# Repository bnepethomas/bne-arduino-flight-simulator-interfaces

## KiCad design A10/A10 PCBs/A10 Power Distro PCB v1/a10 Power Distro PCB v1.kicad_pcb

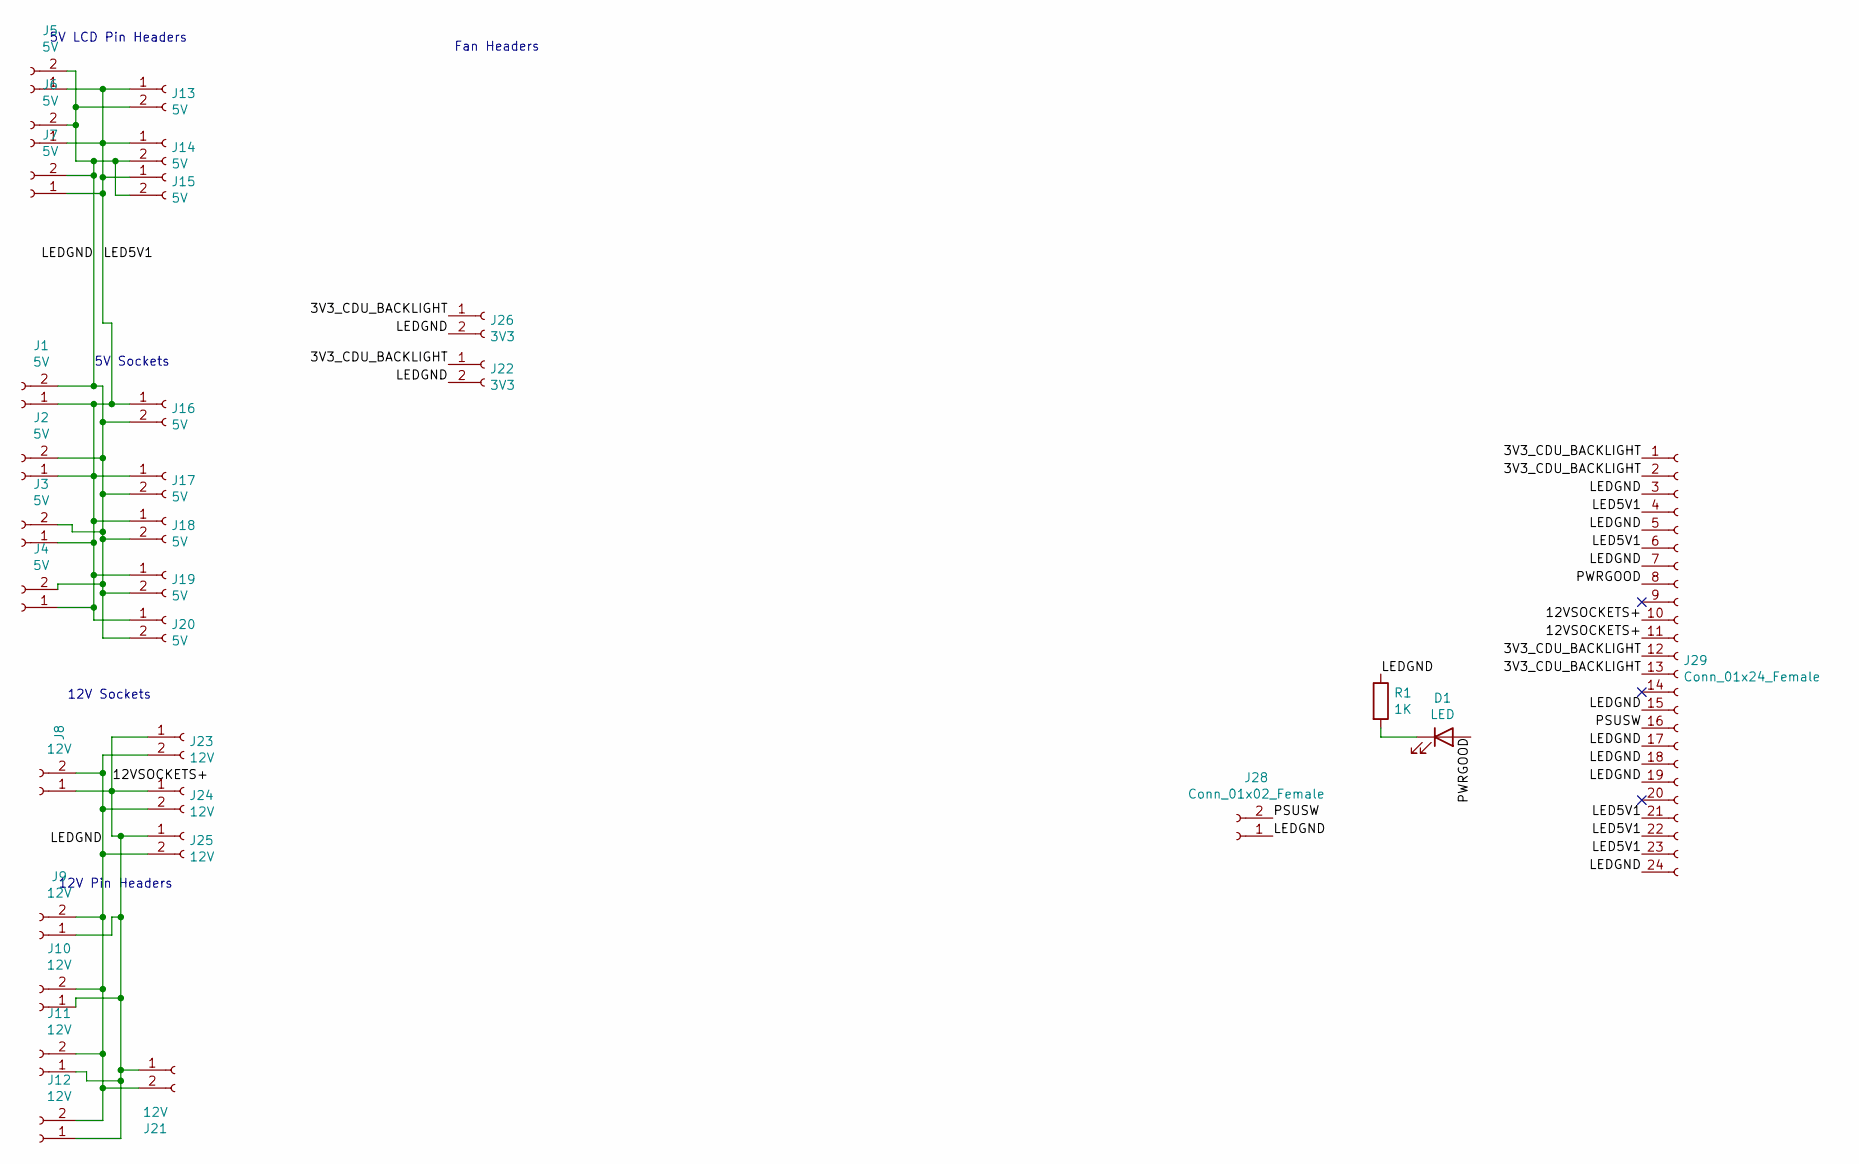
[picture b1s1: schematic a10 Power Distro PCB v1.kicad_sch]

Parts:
D1: LED; LED_D3.0mm
J1, J2, J3, J4, J16, J17, J18: 5V; BarrelJack_Horizontal
J5, J6, J7, J13, J14, J15, J19, J20: 5V; Molex_KK-254_AE-6410-02A_1x02_P2.54mm_Vertical
J8, J11, J12, J23, J24, J25: 12V; BarrelJack_Horizontal
J9, J10, J21: 12V; Molex_KK-254_AE-6410-02A_1x02_P2.54mm_Vertical
J22: 3V3; BarrelJack_Horizontal
J26: 3V3; Molex_KK-254_AE-6410-02A_1x02_P2.54mm_Vertical
J28: Conn_01x02_Female; Molex_KK-254_AE-6410-02A_1x02_P2.54mm_Vertical
J29: Conn_01x24_Female; Molex_Mini-Fit_Jr_5566-24A_2x12_P4.20mm_Vertical
R1: 1K; R_Axial_DIN0207_L6.3mm_D2.5mm_P7.62mm_Horizontal

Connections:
/3V3_CDU_BACKLIGHT: J22.1, J26.1, J29.1, J29.2, J29.12, J29.13
/12VSOCKETS+: J8.1, J9.1, J10.1, J11.1, J12.1, J21.1, J23.1, J24.1, J25.1, J29.10, J29.11
/LED5V1: J1.1, J2.1, J3.1, J4.1, J5.1, J6.1, J7.1, J13.1, J14.1, J15.1, J16.1, J17.1, J18.1, J19.1, J20.1, J29.4, J29.6, J29.21, J29.22, J29.23
/LEDGND: J1.2, J2.2, J3.2, J4.2, J5.2, J6.2, J7.2, J8.2, J9.2, J10.2, J11.2, J12.2, J13.2, J14.2, J15.2, J16.2, J17.2, J18.2, J19.2, J20.2, J21.2, J22.2, J23.2, J24.2, J25.2, J26.2, J28.1, J29.3, J29.5, J29.7, J29.15, J29.17, J29.18, J29.19, J29.24, R1.1
/PSUSW: J28.2, J29.16
/PWRGOOD: D1.2 (A), J29.8
unnamed: D1.1 (K), R1.2

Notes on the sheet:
Fan Headers
12V Pin Headers
5V LCD Pin Headers
12V Sockets
5V Sockets

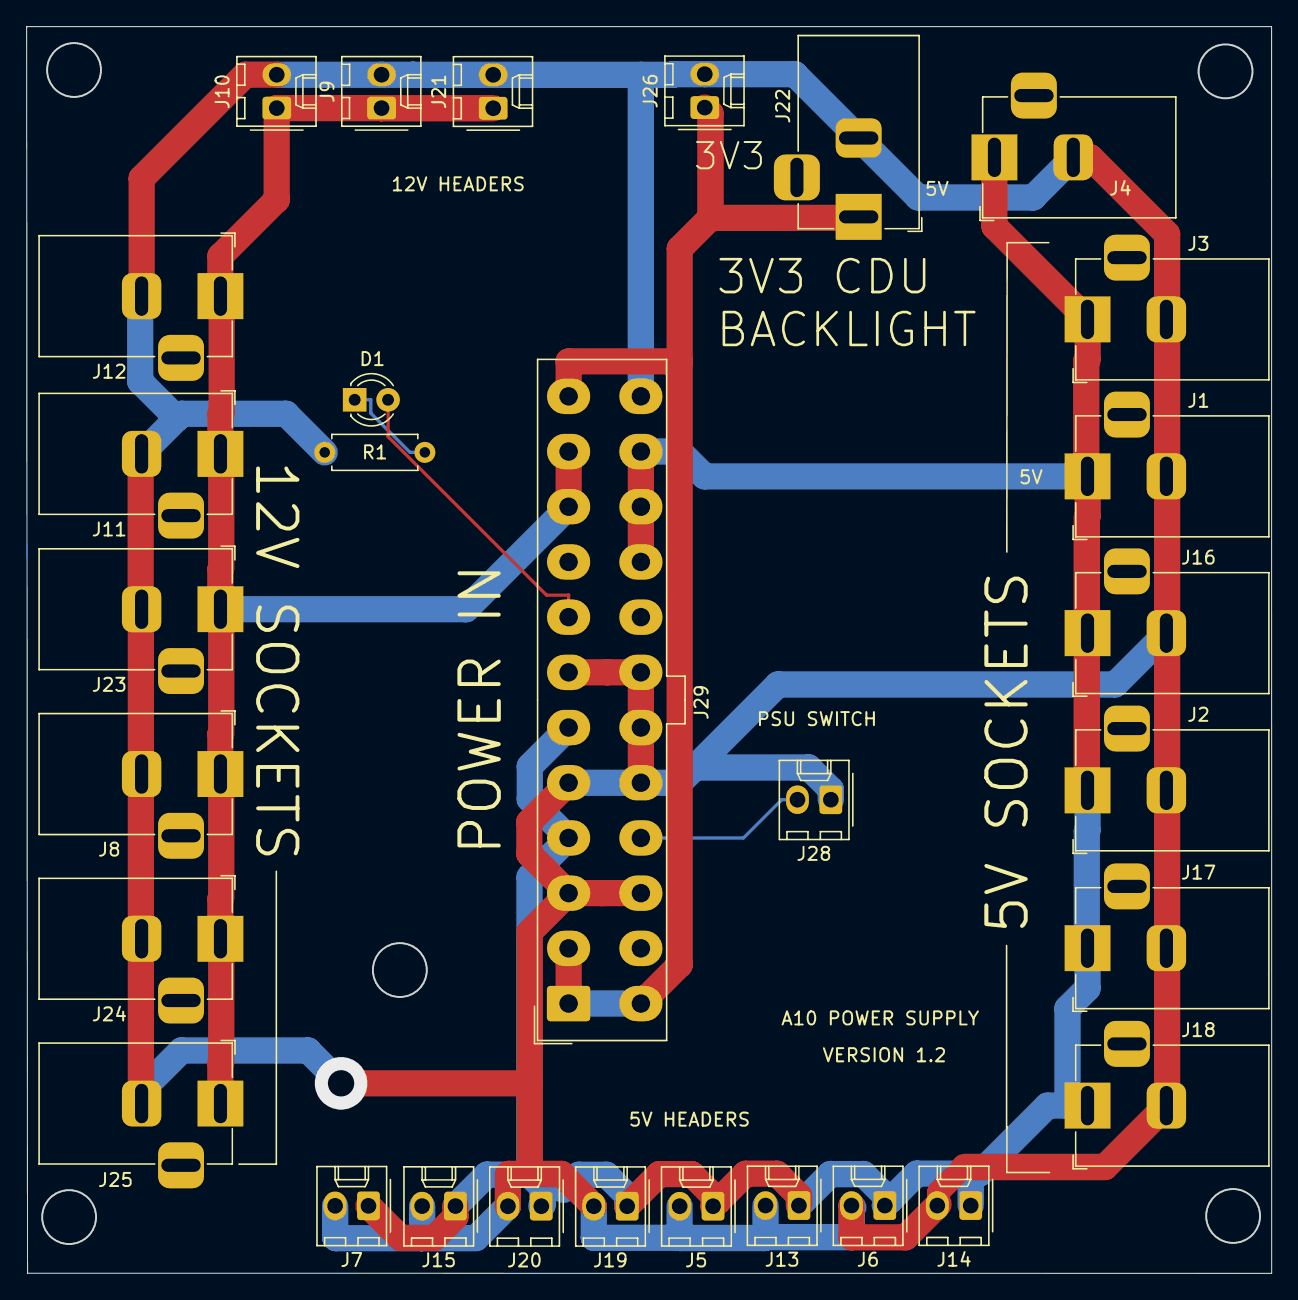
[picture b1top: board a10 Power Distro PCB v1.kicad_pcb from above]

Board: 2 copper layers, 94.7 x 94.9 mm, 30 parts (0 on the bottom side), 7 nets.

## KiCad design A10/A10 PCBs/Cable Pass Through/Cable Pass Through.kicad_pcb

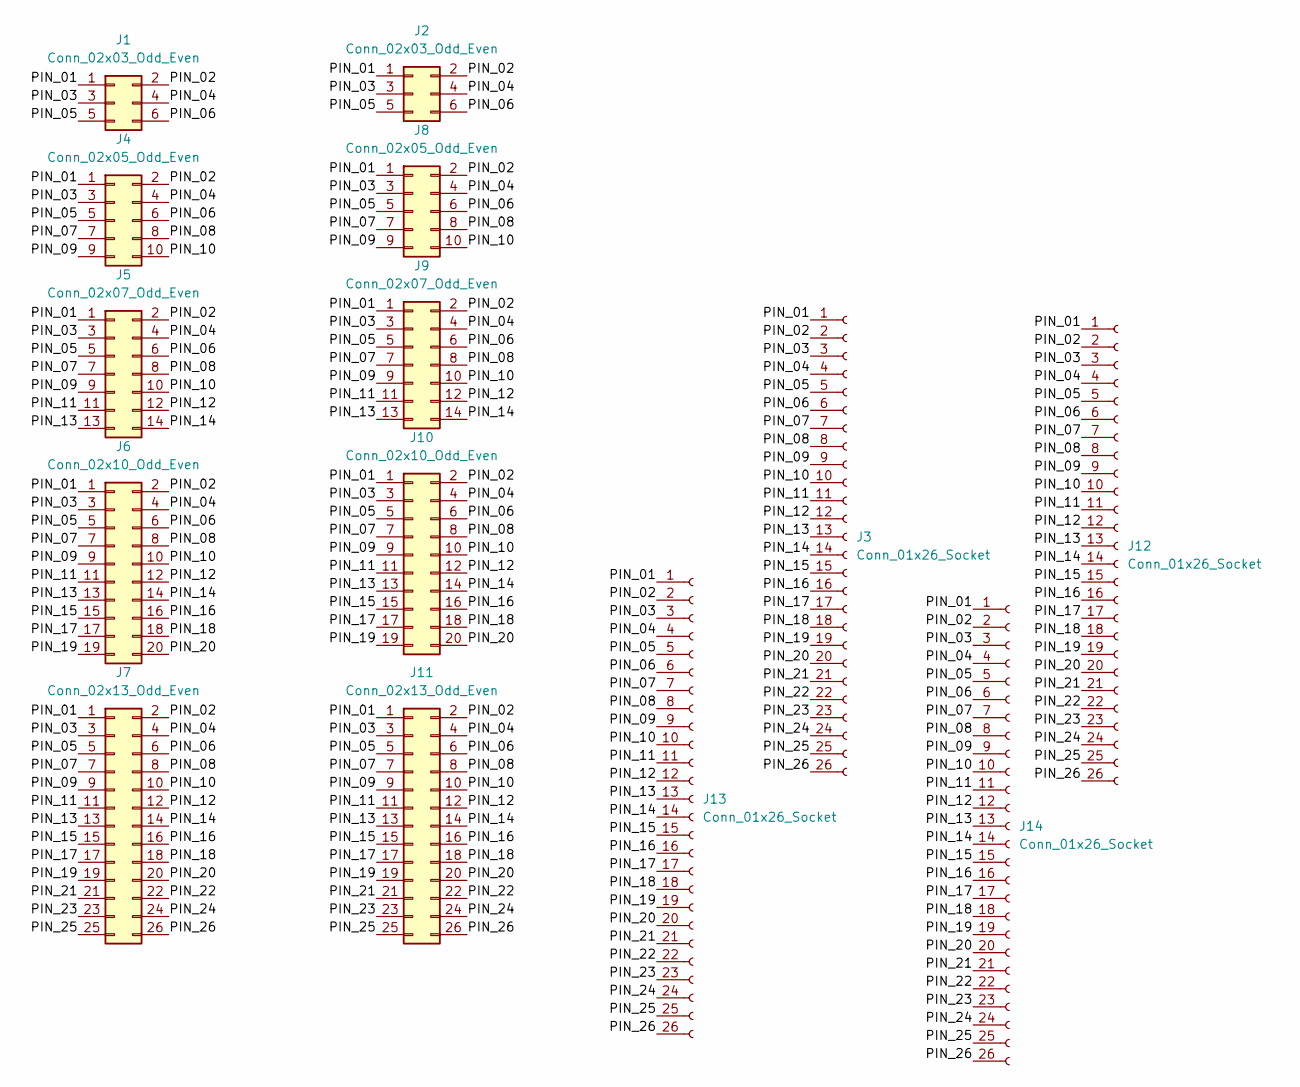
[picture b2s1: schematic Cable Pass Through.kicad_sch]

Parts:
J1, J2: Conn_02x03_Odd_Even; IDC-Header_2x03_P2.54mm_Vertical
J3, J12, J13, J14: Conn_01x26_Socket; PinHeader_1x26_P2.54mm_Vertical
J4, J8: Conn_02x05_Odd_Even; IDC-Header_2x05_P2.54mm_Vertical
J5, J9: Conn_02x07_Odd_Even; IDC-Header_2x07_P2.54mm_Vertical
J6, J10: Conn_02x10_Odd_Even; IDC-Header_2x10_P2.54mm_Vertical
J7, J11: Conn_02x13_Odd_Even; IDC-Header_2x13_P2.54mm_Vertical

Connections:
/PIN_01: J1.1, J2.1, J3.1, J4.1, J5.1, J6.1, J7.1, J8.1, J9.1, J10.1, J11.1, J12.1, J13.1, J14.1
/PIN_02: J1.2, J2.2, J3.2, J4.2, J5.2, J6.2, J7.2, J8.2, J9.2, J10.2, J11.2, J12.2, J13.2, J14.2
/PIN_03: J1.3, J2.3, J3.3, J4.3, J5.3, J6.3, J7.3, J8.3, J9.3, J10.3, J11.3, J12.3, J13.3, J14.3
/PIN_04: J1.4, J2.4, J3.4, J4.4, J5.4, J6.4, J7.4, J8.4, J9.4, J10.4, J11.4, J12.4, J13.4, J14.4
/PIN_05: J1.5, J2.5, J3.5, J4.5, J5.5, J6.5, J7.5, J8.5, J9.5, J10.5, J11.5, J12.5, J13.5, J14.5
/PIN_06: J1.6, J2.6, J3.6, J4.6, J5.6, J6.6, J7.6, J8.6, J9.6, J10.6, J11.6, J12.6, J13.6, J14.6
/PIN_07: J3.7, J4.7, J5.7, J6.7, J7.7, J8.7, J9.7, J10.7, J11.7, J12.7, J13.7, J14.7
/PIN_08: J3.8, J4.8, J5.8, J6.8, J7.8, J8.8, J9.8, J10.8, J11.8, J12.8, J13.8, J14.8
/PIN_09: J3.9, J4.9, J5.9, J6.9, J7.9, J8.9, J9.9, J10.9, J11.9, J12.9, J13.9, J14.9
/PIN_10: J3.10, J4.10, J5.10, J6.10, J7.10, J8.10, J9.10, J10.10, J11.10, J12.10, J13.10, J14.10
/PIN_11: J3.11, J5.11, J6.11, J7.11, J9.11, J10.11, J11.11, J12.11, J13.11, J14.11
/PIN_12: J3.12, J5.12, J6.12, J7.12, J9.12, J10.12, J11.12, J12.12, J13.12, J14.12
/PIN_13: J3.13, J5.13, J6.13, J7.13, J9.13, J10.13, J11.13, J12.13, J13.13, J14.13
/PIN_14: J3.14, J5.14, J6.14, J7.14, J9.14, J10.14, J11.14, J12.14, J13.14, J14.14
/PIN_15: J3.15, J6.15, J7.15, J10.15, J11.15, J12.15, J13.15, J14.15
/PIN_16: J3.16, J6.16, J7.16, J10.16, J11.16, J12.16, J13.16, J14.16
/PIN_17: J3.17, J6.17, J7.17, J10.17, J11.17, J12.17, J13.17, J14.17
/PIN_18: J3.18, J6.18, J7.18, J10.18, J11.18, J12.18, J13.18, J14.18
/PIN_19: J3.19, J6.19, J7.19, J10.19, J11.19, J12.19, J13.19, J14.19
/PIN_20: J3.20, J6.20, J7.20, J10.20, J11.20, J12.20, J13.20, J14.20
/PIN_21: J3.21, J7.21, J11.21, J12.21, J13.21, J14.21
/PIN_22: J3.22, J7.22, J11.22, J12.22, J13.22, J14.22
/PIN_23: J3.23, J7.23, J11.23, J12.23, J13.23, J14.23
/PIN_24: J3.24, J7.24, J11.24, J12.24, J13.24, J14.24
/PIN_25: J3.25, J7.25, J11.25, J12.25, J13.25, J14.25
/PIN_26: J3.26, J7.26, J11.26, J12.26, J13.26, J14.26

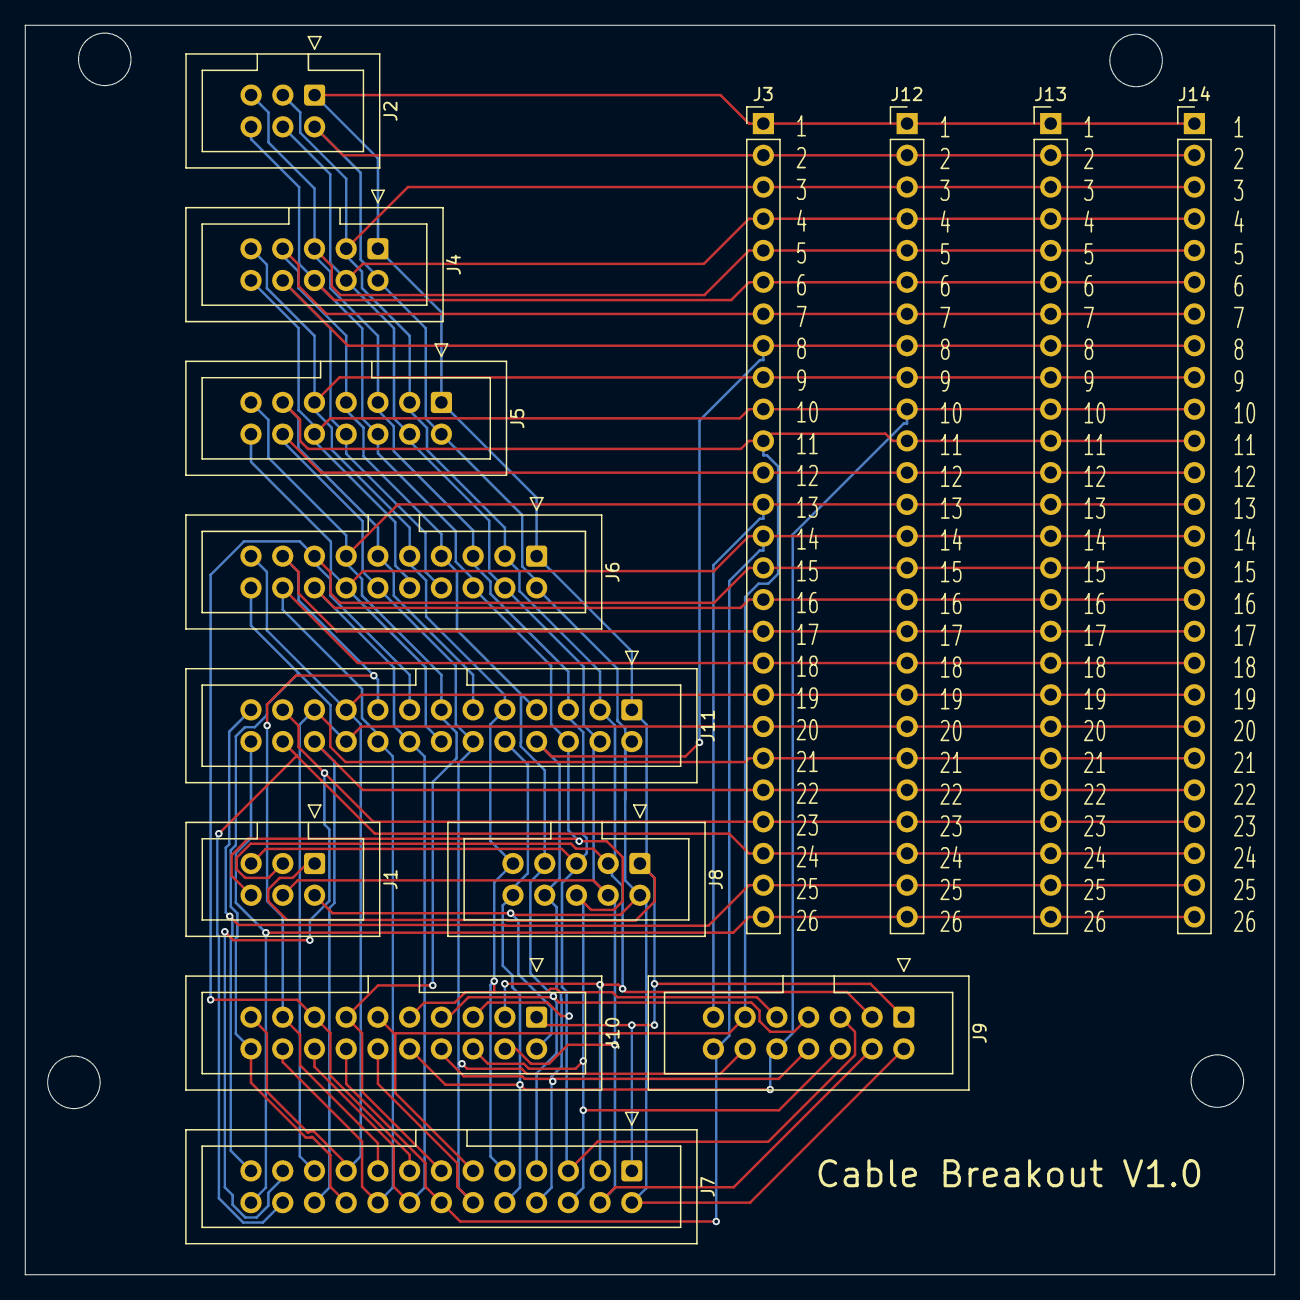
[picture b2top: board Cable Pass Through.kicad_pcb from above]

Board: 2 copper layers, 100.0 x 100.0 mm, 14 parts (0 on the bottom side), 26 nets.

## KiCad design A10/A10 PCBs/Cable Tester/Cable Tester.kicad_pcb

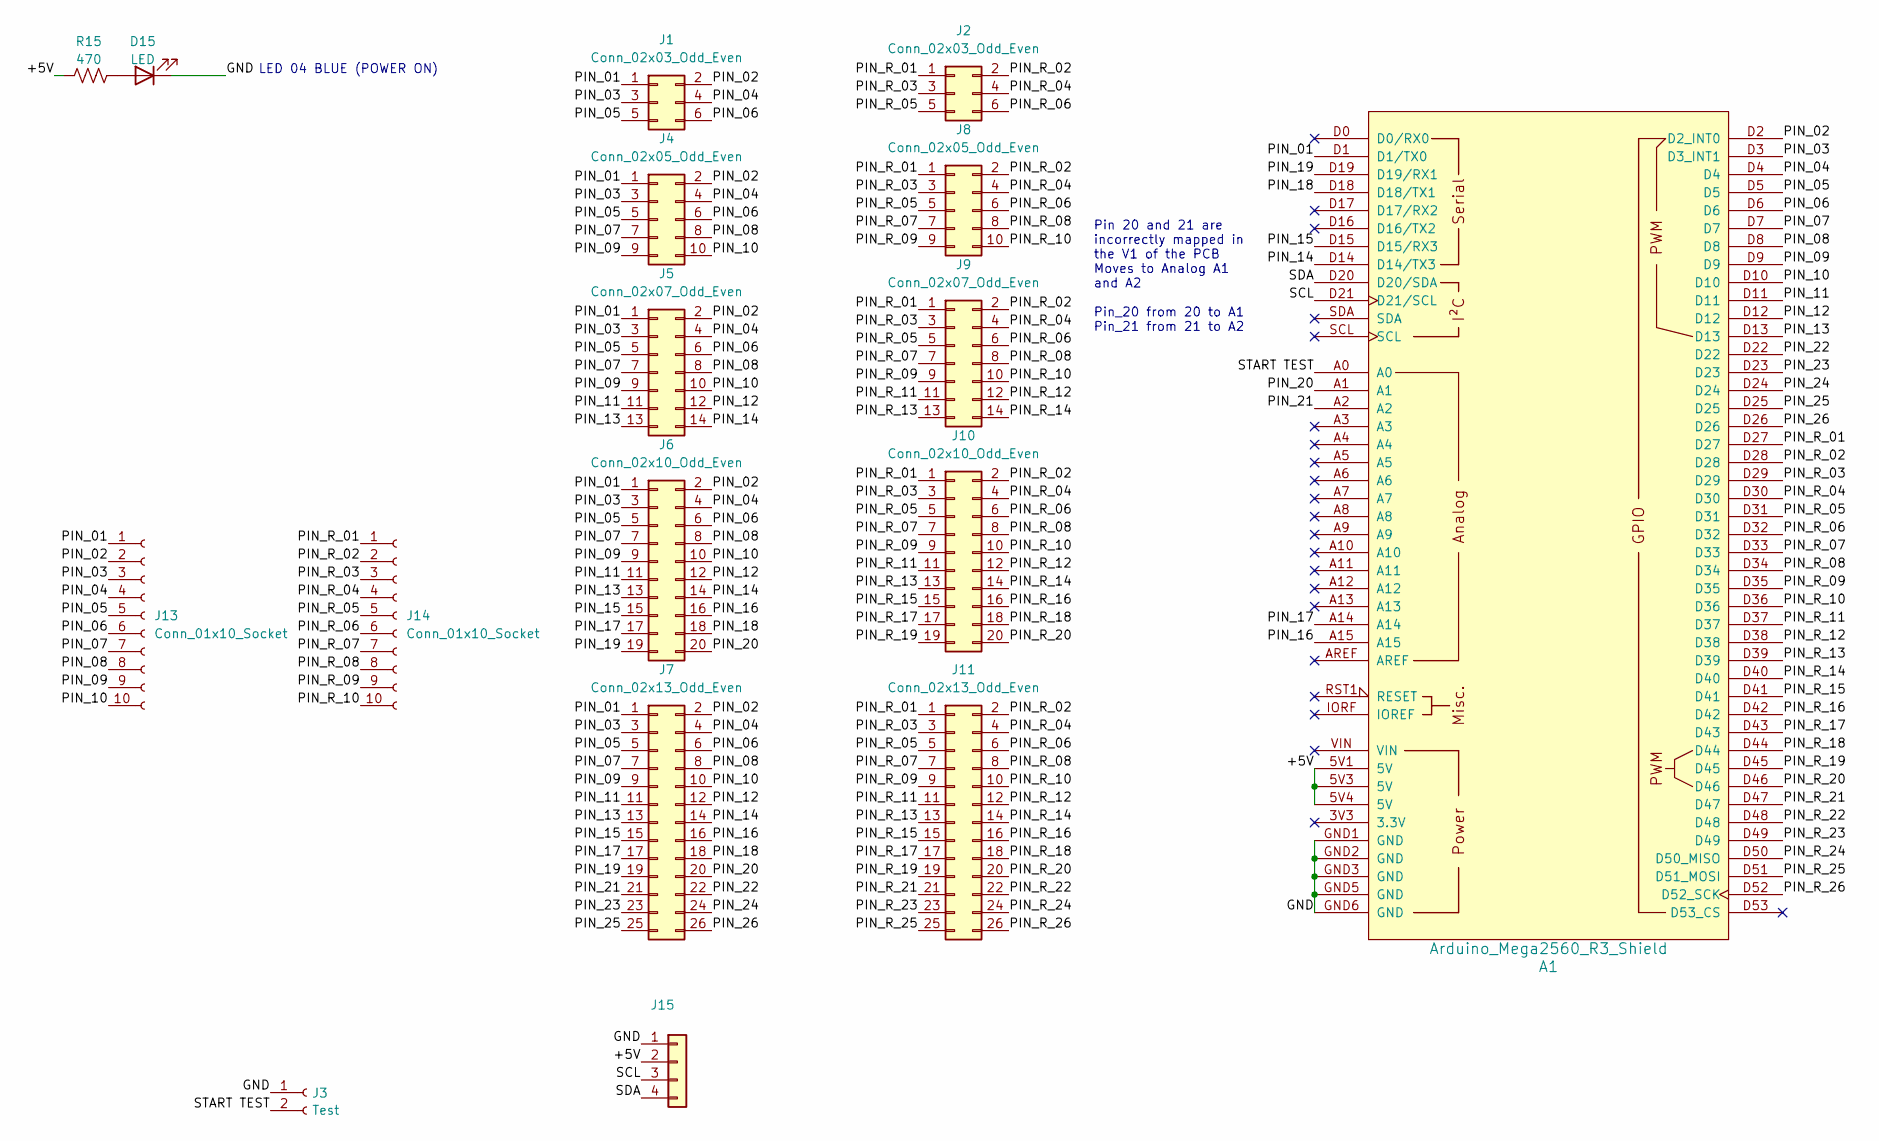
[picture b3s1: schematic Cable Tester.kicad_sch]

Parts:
A1: Arduino_Mega2560_R3_Shield
D15: LED; LED_D3.0mm
J1, J2: Conn_02x03_Odd_Even; IDC-Header_2x03_P2.54mm_Vertical
J3: Test; JST_XA_B02B-XASK-1_1x02_P2.50mm_Vertical
J4, J8: Conn_02x05_Odd_Even; IDC-Header_2x05_P2.54mm_Vertical
J5, J9: Conn_02x07_Odd_Even; IDC-Header_2x07_P2.54mm_Vertical
J6, J10: Conn_02x10_Odd_Even; IDC-Header_2x10_P2.54mm_Vertical
J7, J11: Conn_02x13_Odd_Even; IDC-Header_2x13_P2.54mm_Vertical
J13, J14: Conn_01x10_Socket; PinHeader_1x10_P2.54mm_Vertical
J15: PT_Conn_01x04; Molex_KK-254_AE-6410-04A_1x04_P2.54mm_Vertical
R15: 470; R_Axial_DIN0204_L3.6mm_D1.6mm_P2.54mm_Vertical

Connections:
/+5V: A1.5V1 (5V), A1.5V3 (5V), A1.5V4 (5V), J15.2, R15.1
/GND: A1.GND1 (GND), A1.GND2 (GND), A1.GND3 (GND), A1.GND5 (GND), A1.GND6 (GND), D15.1 (K), J3.1, J15.1
/PIN_01: A1.D1 (D1/TX0), J1.1, J4.1, J5.1, J6.1, J7.1, J13.1
/PIN_02: A1.D2 (D2_INT0), J1.2, J4.2, J5.2, J6.2, J7.2, J13.2
/PIN_03: A1.D3 (D3_INT1), J1.3, J4.3, J5.3, J6.3, J7.3, J13.3
/PIN_04: A1.D4, J1.4, J4.4, J5.4, J6.4, J7.4, J13.4
/PIN_05: A1.D5, J1.5, J4.5, J5.5, J6.5, J7.5, J13.5
/PIN_06: A1.D6, J1.6, J4.6, J5.6, J6.6, J7.6, J13.6
/PIN_07: A1.D7, J4.7, J5.7, J6.7, J7.7, J13.7
/PIN_08: A1.D8, J4.8, J5.8, J6.8, J7.8, J13.8
/PIN_09: A1.D9, J4.9, J5.9, J6.9, J7.9, J13.9
/PIN_10: A1.D10, J4.10, J5.10, J6.10, J7.10, J13.10
/PIN_11: A1.D11, J5.11, J6.11, J7.11
/PIN_12: A1.D12, J5.12, J6.12, J7.12
/PIN_13: A1.D13, J5.13, J6.13, J7.13
/PIN_14: A1.D14 (D14/TX3), J5.14, J6.14, J7.14
/PIN_15: A1.D15 (D15/RX3), J6.15, J7.15
/PIN_16: A1.A15, J6.16, J7.16
/PIN_17: A1.A14, J6.17, J7.17
/PIN_18: A1.D18 (D18/TX1), J6.18, J7.18
/PIN_19: A1.D19 (D19/RX1), J6.19, J7.19
/PIN_20: A1.A1, J6.20, J7.20
/PIN_21: A1.A2, J7.21
/PIN_22: A1.D22, J7.22
/PIN_23: A1.D23, J7.23
/PIN_24: A1.D24, J7.24
/PIN_25: A1.D25, J7.25
/PIN_26: A1.D26, J7.26
/PIN_R_01: A1.D27, J2.1, J8.1, J9.1, J10.1, J11.1, J14.1
/PIN_R_02: A1.D28, J2.2, J8.2, J9.2, J10.2, J11.2, J14.2
/PIN_R_03: A1.D29, J2.3, J8.3, J9.3, J10.3, J11.3, J14.3
/PIN_R_04: A1.D30, J2.4, J8.4, J9.4, J10.4, J11.4, J14.4
/PIN_R_05: A1.D31, J2.5, J8.5, J9.5, J10.5, J11.5, J14.5
/PIN_R_06: A1.D32, J2.6, J8.6, J9.6, J10.6, J11.6, J14.6
/PIN_R_07: A1.D33, J8.7, J9.7, J10.7, J11.7, J14.7
/PIN_R_08: A1.D34, J8.8, J9.8, J10.8, J11.8, J14.8
/PIN_R_09: A1.D35, J8.9, J9.9, J10.9, J11.9, J14.9
/PIN_R_10: A1.D36, J8.10, J9.10, J10.10, J11.10, J14.10
/PIN_R_11: A1.D37, J9.11, J10.11, J11.11
/PIN_R_12: A1.D38, J9.12, J10.12, J11.12
/PIN_R_13: A1.D39, J9.13, J10.13, J11.13
/PIN_R_14: A1.D40, J9.14, J10.14, J11.14
/PIN_R_15: A1.D41, J10.15, J11.15
/PIN_R_16: A1.D42, J10.16, J11.16
/PIN_R_17: A1.D43, J10.17, J11.17
/PIN_R_18: A1.D44, J10.18, J11.18
/PIN_R_19: A1.D45, J10.19, J11.19
/PIN_R_20: A1.D46, J10.20, J11.20
/PIN_R_21: A1.D47, J11.21
/PIN_R_22: A1.D48, J11.22
/PIN_R_23: A1.D49, J11.23
/PIN_R_24: A1.D50 (D50_MISO), J11.24
/PIN_R_25: A1.D51 (D51_MOSI), J11.25
/PIN_R_26: A1.D52 (D52_SCK), J11.26
/SCL: A1.D21 (D21/SCL), J15.3
/SDA: A1.D20 (D20/SDA), J15.4
/START TEST: A1.A0, J3.2
unnamed: D15.2 (A), R15.2

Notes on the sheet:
Pin 20 and 21 are incorrectly mapped in the V1 of the PCB Moves to Analog A1 and A2 Pin_20 from 20 to A1 Pin_21 from 21 to A2
LED 04 BLUE (POWER ON)

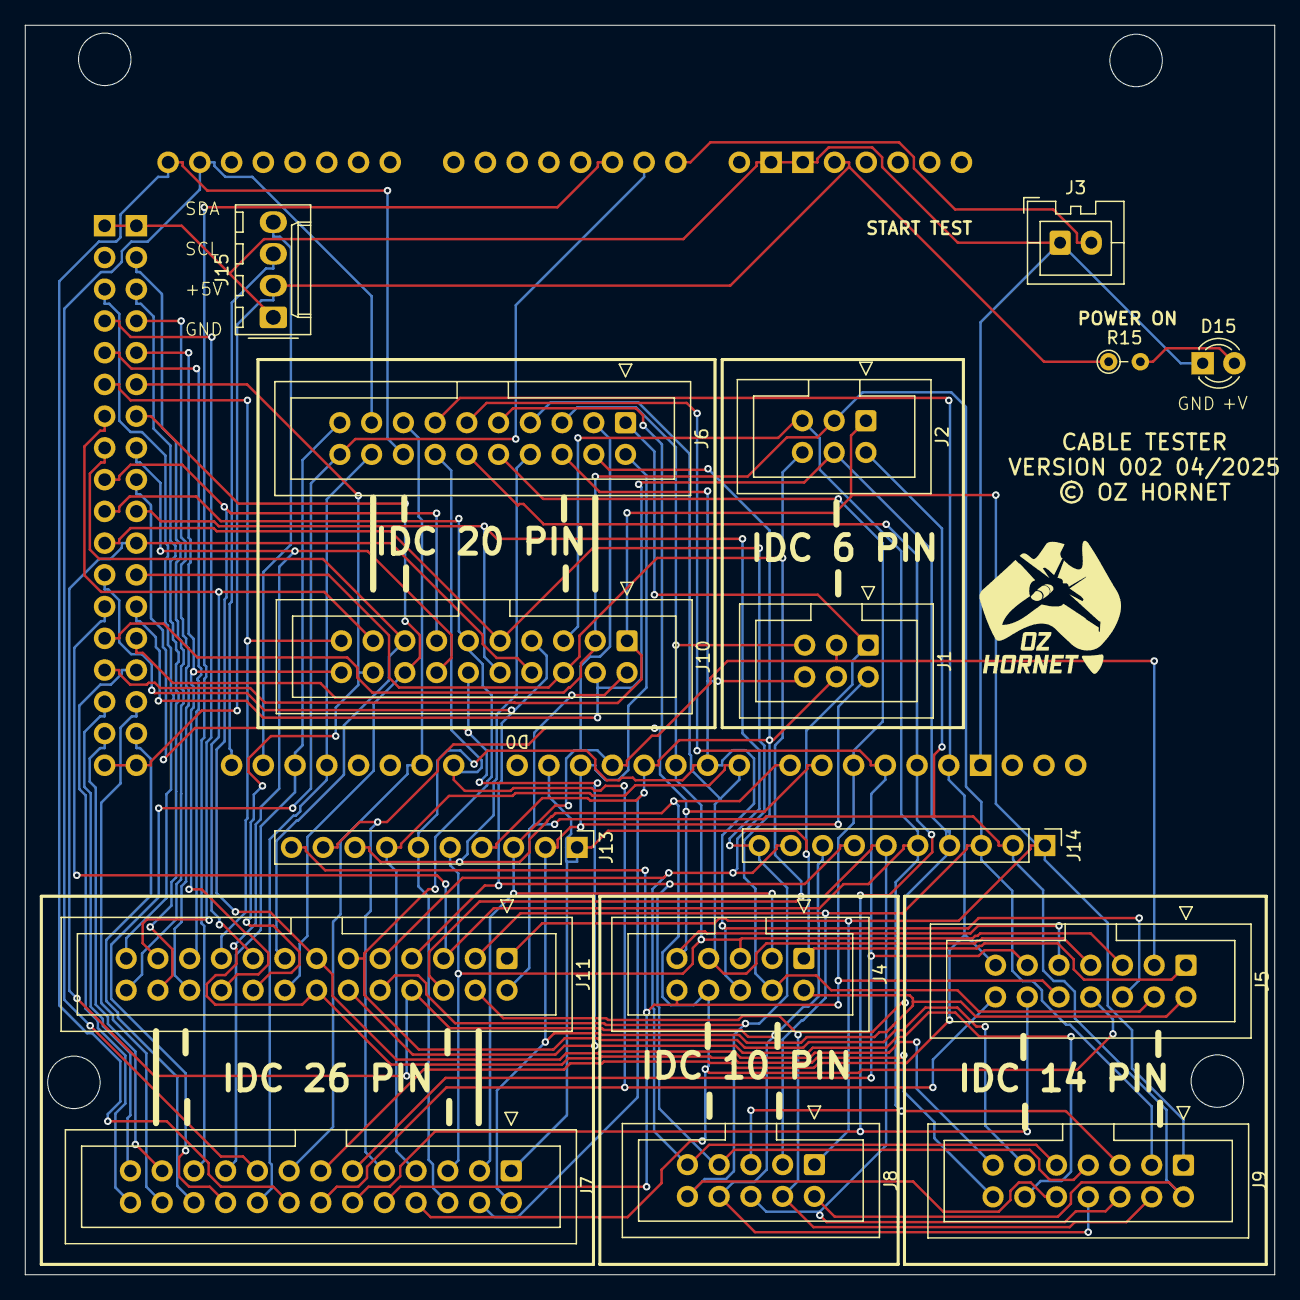
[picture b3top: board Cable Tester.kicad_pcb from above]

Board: 2 copper layers, 100.0 x 100.0 mm, 17 parts (0 on the bottom side), 58 nets.

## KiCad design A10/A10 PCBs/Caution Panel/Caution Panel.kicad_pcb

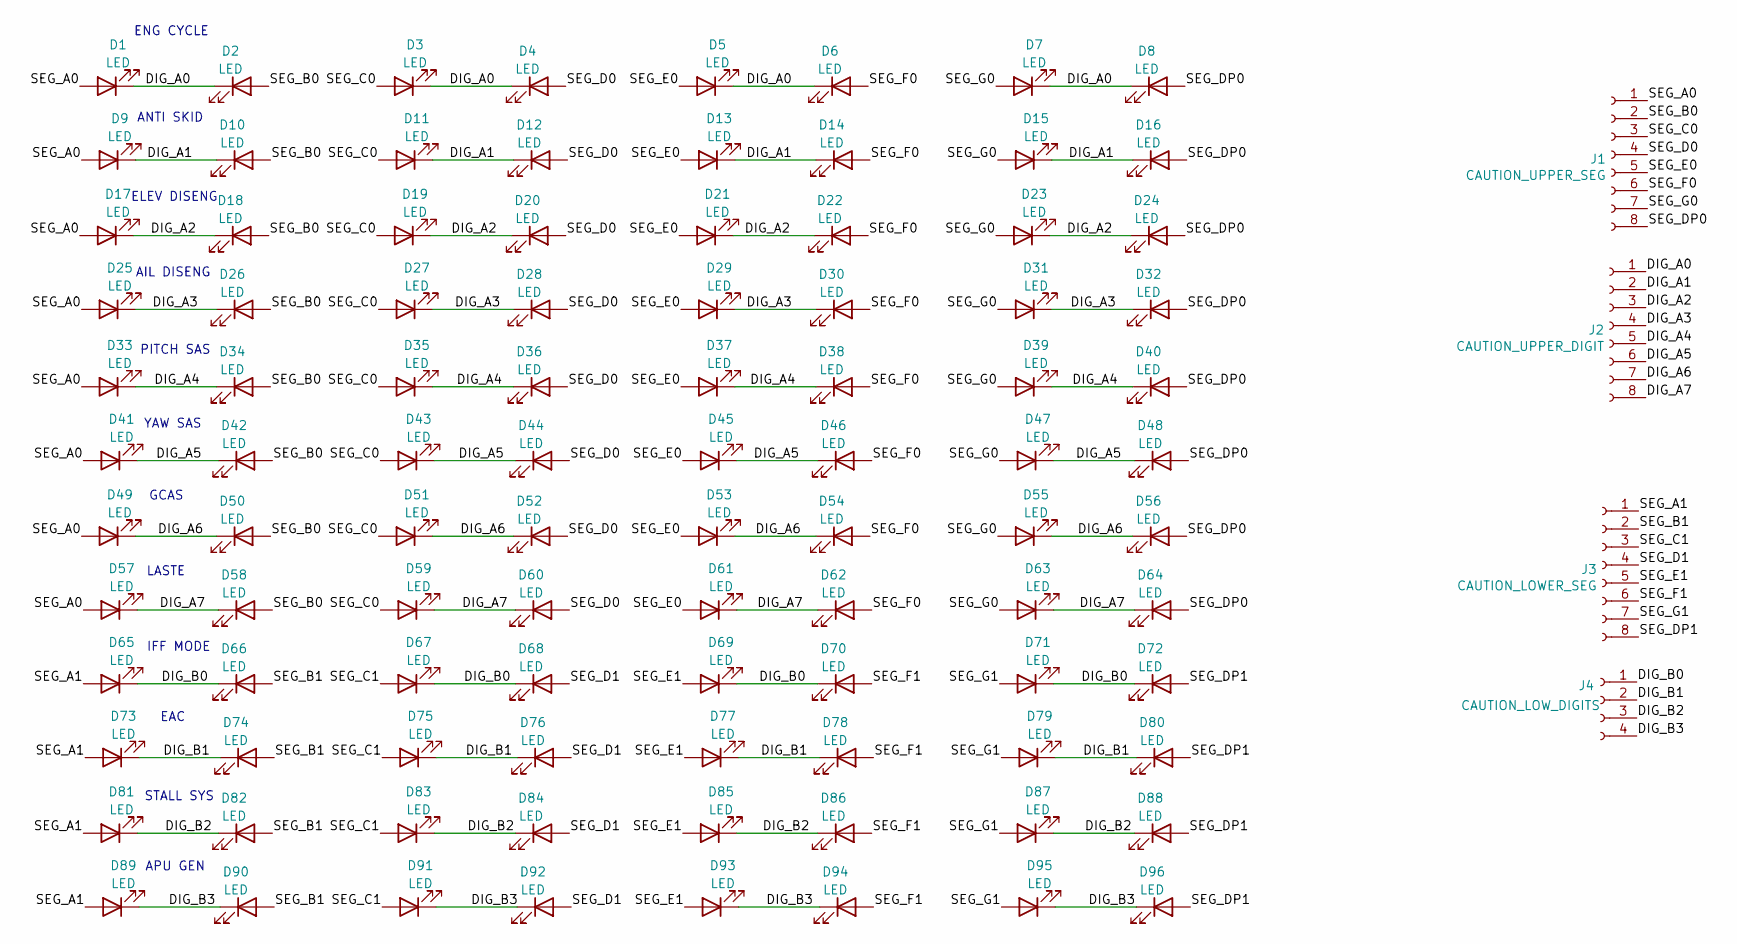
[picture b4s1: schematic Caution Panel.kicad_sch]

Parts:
D1, D2, D3, D4, D5, D6, D7, D8, D9, D10, D11, D12, D13, D14, D15, D16, D17, D18, D19, D20, D21, D22, D23, D24, D25, D26, D27, D28, D29, D30, D31, D32, D33, D34, D35, D36, D37, D38, D39, D40, D41, D42, D43, D44, D45, D46, D47, D48, D49, D50, D51, D52, D53, D54, D55, D56, D57, D58, D59, D60, D61, D62, D63, D64, D65, D66, D67, D68, D69, D70, D71, D72, D73, D74, D75, D76, D77, D78, D79, D80, D81, D82, D83, D84, D85, D86, D87, D88, D89, D90, D91, D92, D93, D94, D95, D96: LED; LED_D5.0mm
J1: CAUTION_UPPER_SEG; Molex_KK-254_AE-6410-08A_1x08_P2.54mm_Vertical
J2: CAUTION_UPPER_DIGIT; Molex_KK-254_AE-6410-08A_1x08_P2.54mm_Vertical
J3: CAUTION_LOWER_SEG; Molex_KK-254_AE-6410-08A_1x08_P2.54mm_Vertical
J4: CAUTION_LOW_DIGITS; Molex_KK-254_AE-6410-04A_1x04_P2.54mm_Vertical

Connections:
/DIG_A0: D1.1 (K), D2.1 (K), D3.1 (K), D4.1 (K), D5.1 (K), D6.1 (K), D7.1 (K), D8.1 (K), J2.1
/DIG_A1: D9.1 (K), D10.1 (K), D11.1 (K), D12.1 (K), D13.1 (K), D14.1 (K), D15.1 (K), D16.1 (K), J2.2
/DIG_A2: D17.1 (K), D18.1 (K), D19.1 (K), D20.1 (K), D21.1 (K), D22.1 (K), D23.1 (K), D24.1 (K), J2.3
/DIG_A3: D25.1 (K), D26.1 (K), D27.1 (K), D28.1 (K), D29.1 (K), D30.1 (K), D31.1 (K), D32.1 (K), J2.4
/DIG_A4: D33.1 (K), D34.1 (K), D35.1 (K), D36.1 (K), D37.1 (K), D38.1 (K), D39.1 (K), D40.1 (K), J2.5
/DIG_A5: D41.1 (K), D42.1 (K), D43.1 (K), D44.1 (K), D45.1 (K), D46.1 (K), D47.1 (K), D48.1 (K), J2.6
/DIG_A6: D49.1 (K), D50.1 (K), D51.1 (K), D52.1 (K), D53.1 (K), D54.1 (K), D55.1 (K), D56.1 (K), J2.7
/DIG_A7: D57.1 (K), D58.1 (K), D59.1 (K), D60.1 (K), D61.1 (K), D62.1 (K), D63.1 (K), D64.1 (K), J2.8
/DIG_B0: D65.1 (K), D66.1 (K), D67.1 (K), D68.1 (K), D69.1 (K), D70.1 (K), D71.1 (K), D72.1 (K), J4.1
/DIG_B1: D73.1 (K), D74.1 (K), D75.1 (K), D76.1 (K), D77.1 (K), D78.1 (K), D79.1 (K), D80.1 (K), J4.2
/DIG_B2: D81.1 (K), D82.1 (K), D83.1 (K), D84.1 (K), D85.1 (K), D86.1 (K), D87.1 (K), D88.1 (K), J4.3
/DIG_B3: D89.1 (K), D90.1 (K), D91.1 (K), D92.1 (K), D93.1 (K), D94.1 (K), D95.1 (K), D96.1 (K), J4.4
/SEG_A0: D1.2 (A), D9.2 (A), D17.2 (A), D25.2 (A), D33.2 (A), D41.2 (A), D49.2 (A), D57.2 (A), J1.1
/SEG_A1: D65.2 (A), D73.2 (A), D81.2 (A), D89.2 (A), J3.1
/SEG_B0: D2.2 (A), D10.2 (A), D18.2 (A), D26.2 (A), D34.2 (A), D42.2 (A), D50.2 (A), D58.2 (A), J1.2
/SEG_B1: D66.2 (A), D74.2 (A), D82.2 (A), D90.2 (A), J3.2
/SEG_C0: D3.2 (A), D11.2 (A), D19.2 (A), D27.2 (A), D35.2 (A), D43.2 (A), D51.2 (A), D59.2 (A), J1.3
/SEG_C1: D67.2 (A), D75.2 (A), D83.2 (A), D91.2 (A), J3.3
/SEG_D0: D4.2 (A), D12.2 (A), D20.2 (A), D28.2 (A), D36.2 (A), D44.2 (A), D52.2 (A), D60.2 (A), J1.4
/SEG_D1: D68.2 (A), D76.2 (A), D84.2 (A), D92.2 (A), J3.4
/SEG_DP0: D8.2 (A), D16.2 (A), D24.2 (A), D32.2 (A), D40.2 (A), D48.2 (A), D56.2 (A), D64.2 (A), J1.8
/SEG_DP1: D72.2 (A), D80.2 (A), D88.2 (A), D96.2 (A), J3.8
/SEG_E0: D5.2 (A), D13.2 (A), D21.2 (A), D29.2 (A), D37.2 (A), D45.2 (A), D53.2 (A), D61.2 (A), J1.5
/SEG_E1: D69.2 (A), D77.2 (A), D85.2 (A), D93.2 (A), J3.5
/SEG_F0: D6.2 (A), D14.2 (A), D22.2 (A), D30.2 (A), D38.2 (A), D46.2 (A), D54.2 (A), D62.2 (A), J1.6
/SEG_F1: D70.2 (A), D78.2 (A), D86.2 (A), D94.2 (A), J3.6
/SEG_G0: D7.2 (A), D15.2 (A), D23.2 (A), D31.2 (A), D39.2 (A), D47.2 (A), D55.2 (A), D63.2 (A), J1.7
/SEG_G1: D71.2 (A), D79.2 (A), D87.2 (A), D95.2 (A), J3.7

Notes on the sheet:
ELEV DISENG
ANTI SKID
PITCH SAS
STALL SYS
APU GEN
LASTE
EAC
ENG CYCLE
IFF MODE
YAW SAS
GCAS
AIL DISENG

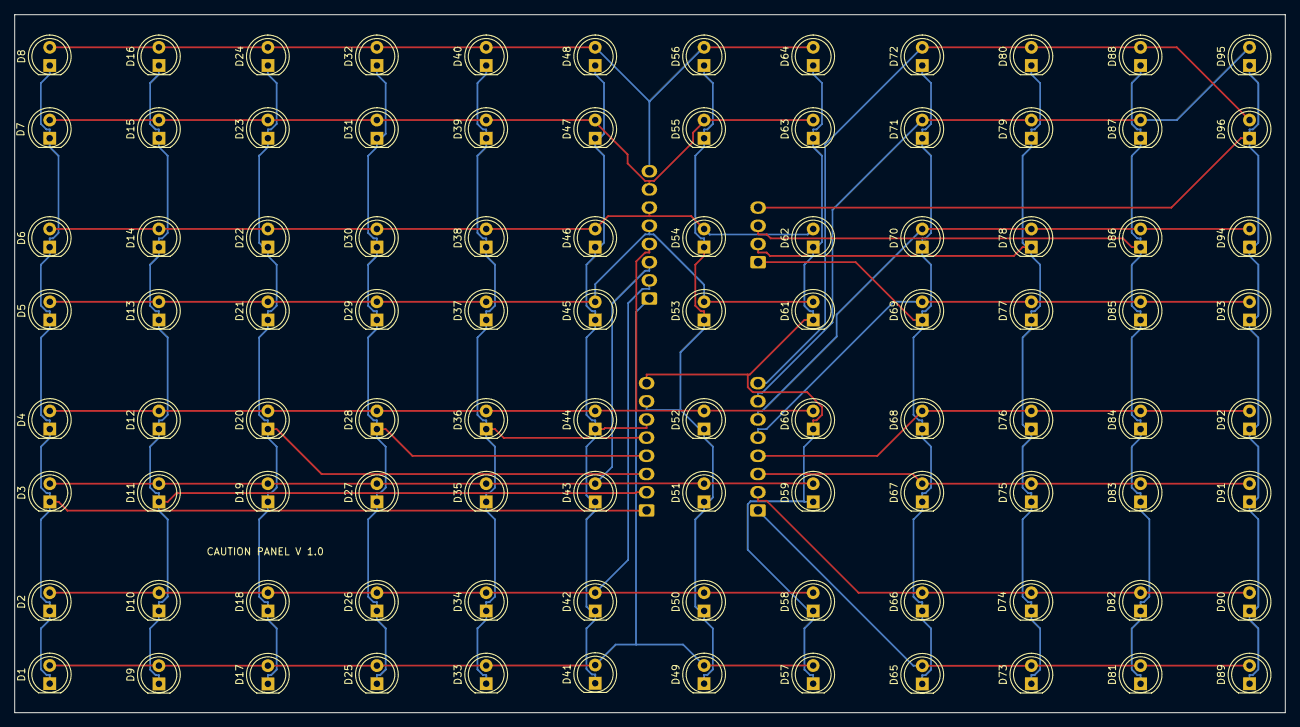
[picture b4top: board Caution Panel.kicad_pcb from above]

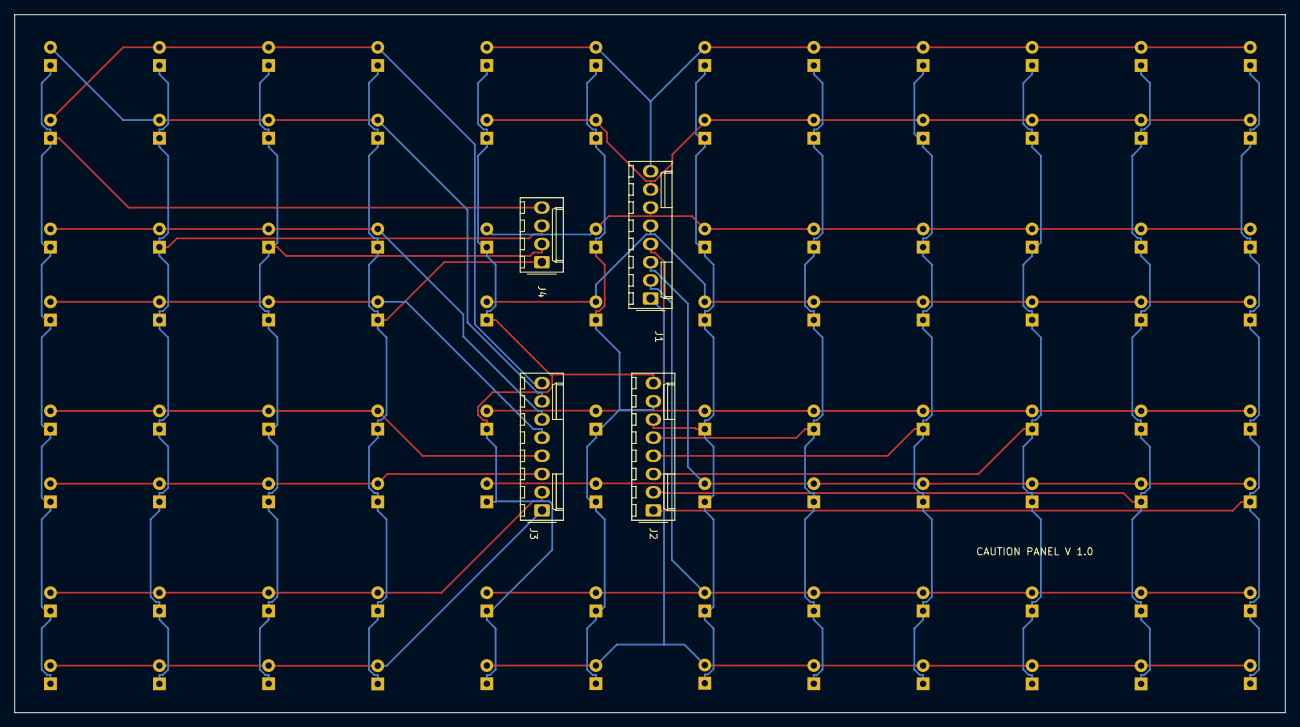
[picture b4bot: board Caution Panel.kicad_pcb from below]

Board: 2 copper layers, 177.5 x 97.5 mm, 100 parts (4 on the bottom side), 28 nets.

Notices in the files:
A10/A10 PCBs/Cable Tester/Cable Tester.kicad_pcb:
© OZ HORNET
